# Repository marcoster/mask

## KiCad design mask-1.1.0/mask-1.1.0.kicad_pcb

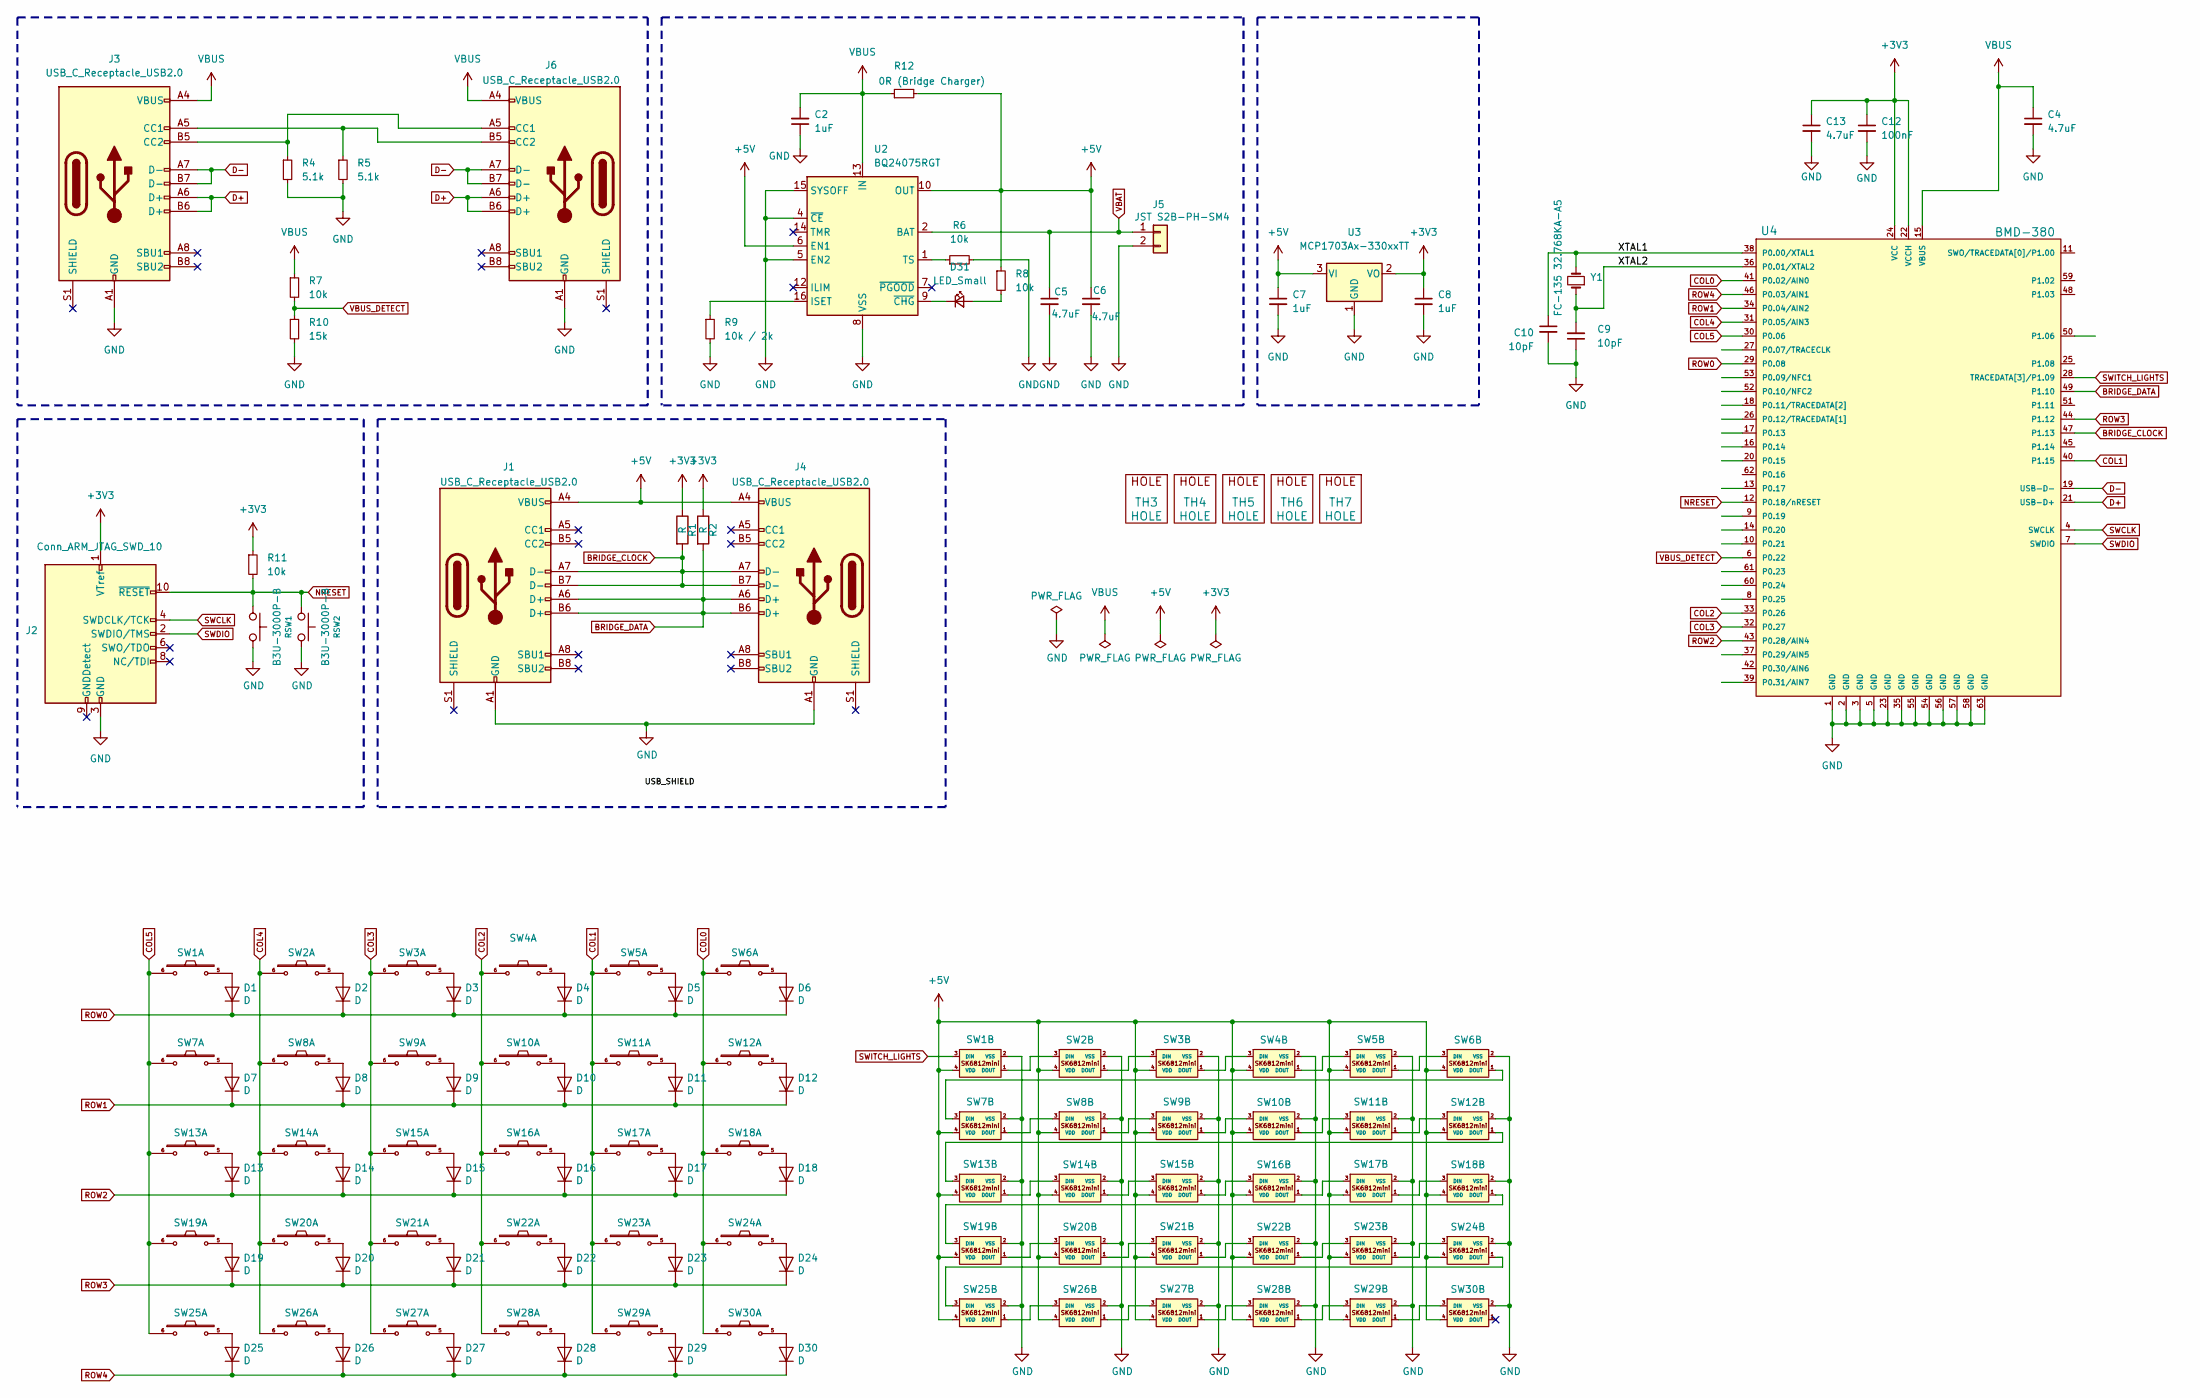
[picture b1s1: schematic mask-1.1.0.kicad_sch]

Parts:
C2, C7, C8: 1uF; C_0603_1608Metric
C4, C5, C6, C13: 4.7uF; C_0603_1608Metric
C9, C10: 10pF; C_0402_1005Metric
C12: 100nF; C_0603_1608Metric
D1, D2, D3, D4, D5, D6, D7, D8, D9, D10, D11, D12, D13, D14, D15, D16, D17, D18, D19, D20, D21, D22, D23, D24, D25, D26, D27, D28, D29, D30: D; crkbd-diode
D31: LED_Small; LED_0603_1608Metric
J1, J6: USB_C_Receptacle_USB2.0; USB_C_Receptacle_GCT_USB4505-xx-A_16P_TopMnt_Horizontal_NO_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
J2: Conn_ARM_JTAG_SWD_10; Tag-Connect_TC2050-IDC-NL_2x05_P1.27mm_Vertical
J3, J4: USB_C_Receptacle_USB2.0; USB_C_Receptacle_GCT_USB4505-xx-A_16P_TopMnt_Horizontal
J5: JST S2B-PH-SM4; JST_PH_S2B-PH-K_1x02_P2.00mm_Horizontal
R1, R2: R; R_0603_1608Metric
R4, R5: 5.1k; R_0603_1608Metric
R6, R7, R8, R11: 10k; R_0603_1608Metric
R9: 10k / 2k; R_0603_1608Metric
R10: 15k; R_0603_1608Metric
R12: 0R (Bridge Charger); R_0603_1608Metric
RSW1, RSW2: B3U-3000P-B; SW_SPST_B3U-3000P-B
SW1, SW2, SW3, SW4, SW5, SW6, SW7, SW8, SW9, SW10, SW11, SW12, SW13, SW14, SW15, SW16, SW17, SW18, SW19, SW20, SW21, SW22, SW23, SW24, SW25, SW26, SW27, SW28, SW29, SW30: SW_PUSH-MX_W_LED; SK6812MINI-E_and_cherry
TH3, TH4, TH5, TH6, TH7: HOLE; HOLE_M2_TH
U2: BQ24075RGT; VQFN-16-1EP_3x3mm_P0.5mm_EP1.6x1.6mm
U3: MCP1703Ax-330xxTT; SOT-23
U4: BMD-380
Y1: FC-135 32.768KA-A5; Crystal_SMD_MicroCrystal_CC7V-T1A-2Pin_3.2x1.5mm

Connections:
+3V3: C8.1, C12.1, C13.1, J2.1 (VTref), R1.1, R2.1, R11.1, U3.2 (VO), U4.22 (VCCH), U4.24 (VCC)
+5V: C6.1, C7.1, J1.A4 (VBUS), J1.A9 (VBUS), J1.B4 (VBUS), J1.B9 (VBUS), J4.A4 (VBUS), J4.A9 (VBUS), J4.B4 (VBUS), J4.B9 (VBUS), R8.1, R12.2, SW1.4 (VDD), SW2.4 (VDD), SW3.4 (VDD), SW4.4 (VDD), SW5.4 (VDD), SW6.4 (VDD), SW7.4 (VDD), SW8.4 (VDD), SW9.4 (VDD), SW10.4 (VDD), SW11.4 (VDD), SW12.4 (VDD), SW13.4 (VDD), SW14.4 (VDD), SW15.4 (VDD), SW16.4 (VDD), SW17.4 (VDD), SW18.4 (VDD), SW19.4 (VDD), SW20.4 (VDD), SW21.4 (VDD), SW22.4 (VDD), SW23.4 (VDD), SW24.4 (VDD), SW25.4 (VDD), SW26.4 (VDD), SW27.4 (VDD), SW28.4 (VDD), SW29.4 (VDD), SW30.4 (VDD), U2.6 (EN1), U2.10 (OUT), U2.11 (OUT), U3.3 (VI)
/XTAL1: C10.1, U4.38 (P0.00/XTAL1), Y1.2
/XTAL2: C9.2, U4.36 (P0.01/XTAL2), Y1.1
BRIDGE_CLOCK: J1.A7 (D-), J1.B7 (D-), J4.A7 (D-), J4.B7 (D-), R1.2, U4.47 (P1.13)
BRIDGE_DATA: J1.A6 (D+), J1.B6 (D+), J4.A6 (D+), J4.B6 (D+), R2.2, U4.49 (P1.10)
COL0: SW6.6, SW12.6, SW18.6, SW24.6, SW30.6, U4.41 (P0.02/AIN0)
COL1: SW5.6, SW11.6, SW17.6, SW23.6, SW29.6, U4.40 (P1.15)
COL2: SW4.6, SW10.6, SW16.6, SW22.6, SW28.6, U4.33 (P0.26)
COL3: SW3.6, SW9.6, SW15.6, SW21.6, SW27.6, U4.32 (P0.27)
COL4: SW2.6, SW8.6, SW14.6, SW20.6, SW26.6, U4.31 (P0.05/AIN3)
COL5: SW1.6, SW7.6, SW13.6, SW19.6, SW25.6, U4.30 (P0.06)
D+: J3.A6 (D+), J3.B6 (D+), J6.A6 (D+), J6.B6 (D+), U4.21 (USB-D+)
D-: J3.A7 (D-), J3.B7 (D-), J6.A7 (D-), J6.B7 (D-), U4.19 (USB-D-)
GND: C2.1, C4.2, C5.2, C6.2, C7.2, C8.2, C9.1, C10.2, C12.2, C13.2, J1.A1 (GND), J1.A12 (GND), J1.B1 (GND), J1.B12 (GND), J2.3 (GND), J2.5 (GND), J3.A1 (GND), J3.A12 (GND), J3.B1 (GND), J3.B12 (GND), J4.A1 (GND), J4.A12 (GND), J4.B1 (GND), J4.B12 (GND), J5.2, J6.A1 (GND), J6.A12 (GND), J6.B1 (GND), J6.B12 (GND), R4.2, R5.2, R6.2, R9.2, R10.2, RSW1.1, RSW2.2, SW1.2 (VSS), SW2.2 (VSS), SW3.2 (VSS), SW4.2 (VSS), SW5.2 (VSS), SW6.2 (VSS), SW7.2 (VSS), SW8.2 (VSS), SW9.2 (VSS), SW10.2 (VSS), SW11.2 (VSS), SW12.2 (VSS), SW13.2 (VSS), SW14.2 (VSS), SW15.2 (VSS), SW16.2 (VSS), SW17.2 (VSS), SW18.2 (VSS), SW19.2 (VSS), SW20.2 (VSS), SW21.2 (VSS), SW22.2 (VSS), SW23.2 (VSS), SW24.2 (VSS), SW25.2 (VSS), SW26.2 (VSS), SW27.2 (VSS), SW28.2 (VSS), SW29.2 (VSS), SW30.2 (VSS), U2.4 (~CE), U2.5 (EN2), U2.8 (VSS), U2.15 (SYSOFF), U2.17 (VSS), U3.1 (GND), U4.1 (GND), U4.2 (GND), U4.3 (GND), U4.5 (GND), U4.23 (GND), U4.35 (GND), U4.54 (GND), U4.55 (GND), U4.56 (GND), U4.57 (GND), U4.58 (GND), U4.63 (GND)
NRESET: J2.10 (~RESET), R11.2, RSW1.2, RSW2.1, U4.12 (P0.18/nRESET)
unnamed: D1.2 (A), SW1.5
unnamed: D2.2 (A), SW2.5
unnamed: D3.2 (A), SW3.5
unnamed: D4.2 (A), SW4.5
unnamed: D5.2 (A), SW5.5
unnamed: D6.2 (A), SW6.5
unnamed: D7.2 (A), SW7.5
unnamed: D8.2 (A), SW8.5
unnamed: D9.2 (A), SW9.5
unnamed: D10.2 (A), SW10.5
unnamed: D11.2 (A), SW11.5
unnamed: D12.2 (A), SW12.5
unnamed: D13.2 (A), SW13.5
unnamed: D14.2 (A), SW14.5
unnamed: D15.2 (A), SW15.5
unnamed: D16.2 (A), SW16.5
unnamed: D17.2 (A), SW17.5
unnamed: D18.2 (A), SW18.5
unnamed: D19.2 (A), SW19.5
unnamed: D20.2 (A), SW20.5
unnamed: D21.2 (A), SW21.5
unnamed: D22.2 (A), SW22.5
unnamed: D23.2 (A), SW23.5
unnamed: D24.2 (A), SW24.5
unnamed: D25.2 (A), SW25.5
unnamed: D26.2 (A), SW26.5
unnamed: D27.2 (A), SW27.5
unnamed: D28.2 (A), SW28.5
unnamed: D29.2 (A), SW29.5
unnamed: D30.2 (A), SW30.5
unnamed: D31.2 (A), R8.2
unnamed: D31.1 (K), U2.9 (~CHG)
unnamed: J3.A5 (CC1), J6.B5 (CC2), R5.1
unnamed: J3.B5 (CC2), J6.A5 (CC1), R4.1
unnamed: SW1.1 (DOUT), SW2.3 (DIN)
unnamed: SW2.1 (DOUT), SW3.3 (DIN)
unnamed: SW3.1 (DOUT), SW4.3 (DIN)
unnamed: SW4.1 (DOUT), SW5.3 (DIN)
unnamed: SW5.1 (DOUT), SW6.3 (DIN)
unnamed: SW6.1 (DOUT), SW7.3 (DIN)
unnamed: SW7.1 (DOUT), SW8.3 (DIN)
unnamed: SW8.1 (DOUT), SW9.3 (DIN)
unnamed: SW9.1 (DOUT), SW10.3 (DIN)
unnamed: SW10.1 (DOUT), SW11.3 (DIN)
unnamed: SW11.1 (DOUT), SW12.3 (DIN)
unnamed: SW12.1 (DOUT), SW13.3 (DIN)
unnamed: SW13.1 (DOUT), SW14.3 (DIN)
unnamed: SW14.1 (DOUT), SW15.3 (DIN)
unnamed: SW15.1 (DOUT), SW16.3 (DIN)
unnamed: SW16.1 (DOUT), SW17.3 (DIN)
unnamed: SW17.1 (DOUT), SW18.3 (DIN)
unnamed: SW18.1 (DOUT), SW19.3 (DIN)
unnamed: SW19.1 (DOUT), SW20.3 (DIN)
unnamed: SW20.1 (DOUT), SW21.3 (DIN)
unnamed: SW21.1 (DOUT), SW22.3 (DIN)
unnamed: SW22.1 (DOUT), SW23.3 (DIN)
unnamed: SW23.1 (DOUT), SW24.3 (DIN)
unnamed: SW24.1 (DOUT), SW25.3 (DIN)
unnamed: SW25.1 (DOUT), SW26.3 (DIN)
unnamed: SW26.1 (DOUT), SW27.3 (DIN)
unnamed: SW27.1 (DOUT), SW28.3 (DIN)
unnamed: SW28.1 (DOUT), SW29.3 (DIN)
unnamed: SW29.1 (DOUT), SW30.3 (DIN)
unnamed: R9.1, U2.16 (ISET)
unnamed: R6.1, U2.1 (TS)
ROW0: D1.1 (K), D2.1 (K), D3.1 (K), D4.1 (K), D5.1 (K), D6.1 (K), U4.29 (P0.08)
ROW1: D7.1 (K), D8.1 (K), D9.1 (K), D10.1 (K), D11.1 (K), D12.1 (K), U4.34 (P0.04/AIN2)
ROW2: D13.1 (K), D14.1 (K), D15.1 (K), D16.1 (K), D17.1 (K), D18.1 (K), U4.43 (P0.28/AIN4)
ROW3: D19.1 (K), D20.1 (K), D21.1 (K), D22.1 (K), D23.1 (K), D24.1 (K), U4.44 (P1.12)
ROW4: D25.1 (K), D26.1 (K), D27.1 (K), D28.1 (K), D29.1 (K), D30.1 (K), U4.46 (P0.03/AIN1)
SWCLK: J2.4 (SWDCLK/TCK), U4.4 (SWCLK)
SWDIO: J2.2 (SWDIO/TMS), U4.7 (SWDIO)
SWITCH_LIGHTS: SW1.3 (DIN), U4.28 (TRACEDATA[3]/P1.09)
VBAT: C5.1, J5.1, U2.2 (BAT), U2.3 (BAT)
VBUS: C2.2, C4.1, J3.A4 (VBUS), J3.A9 (VBUS), J3.B4 (VBUS), J3.B9 (VBUS), J6.A4 (VBUS), J6.A9 (VBUS), J6.B4 (VBUS), J6.B9 (VBUS), R7.1, R12.1, U2.13 (IN), U4.15 (VBUS)
VBUS_DETECT: R7.2, R10.1, U4.6 (P0.22)

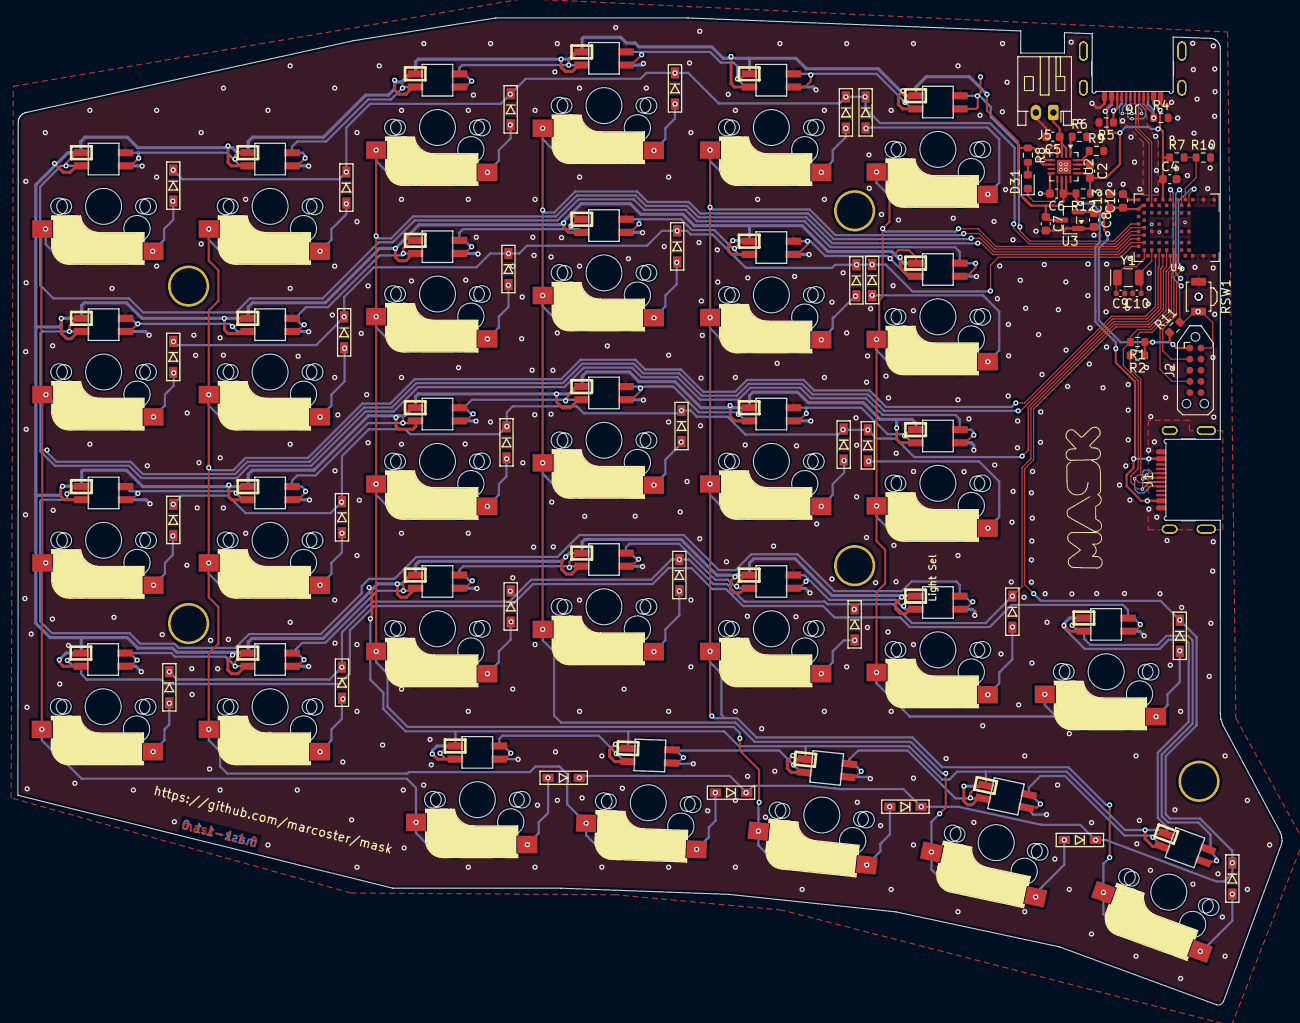
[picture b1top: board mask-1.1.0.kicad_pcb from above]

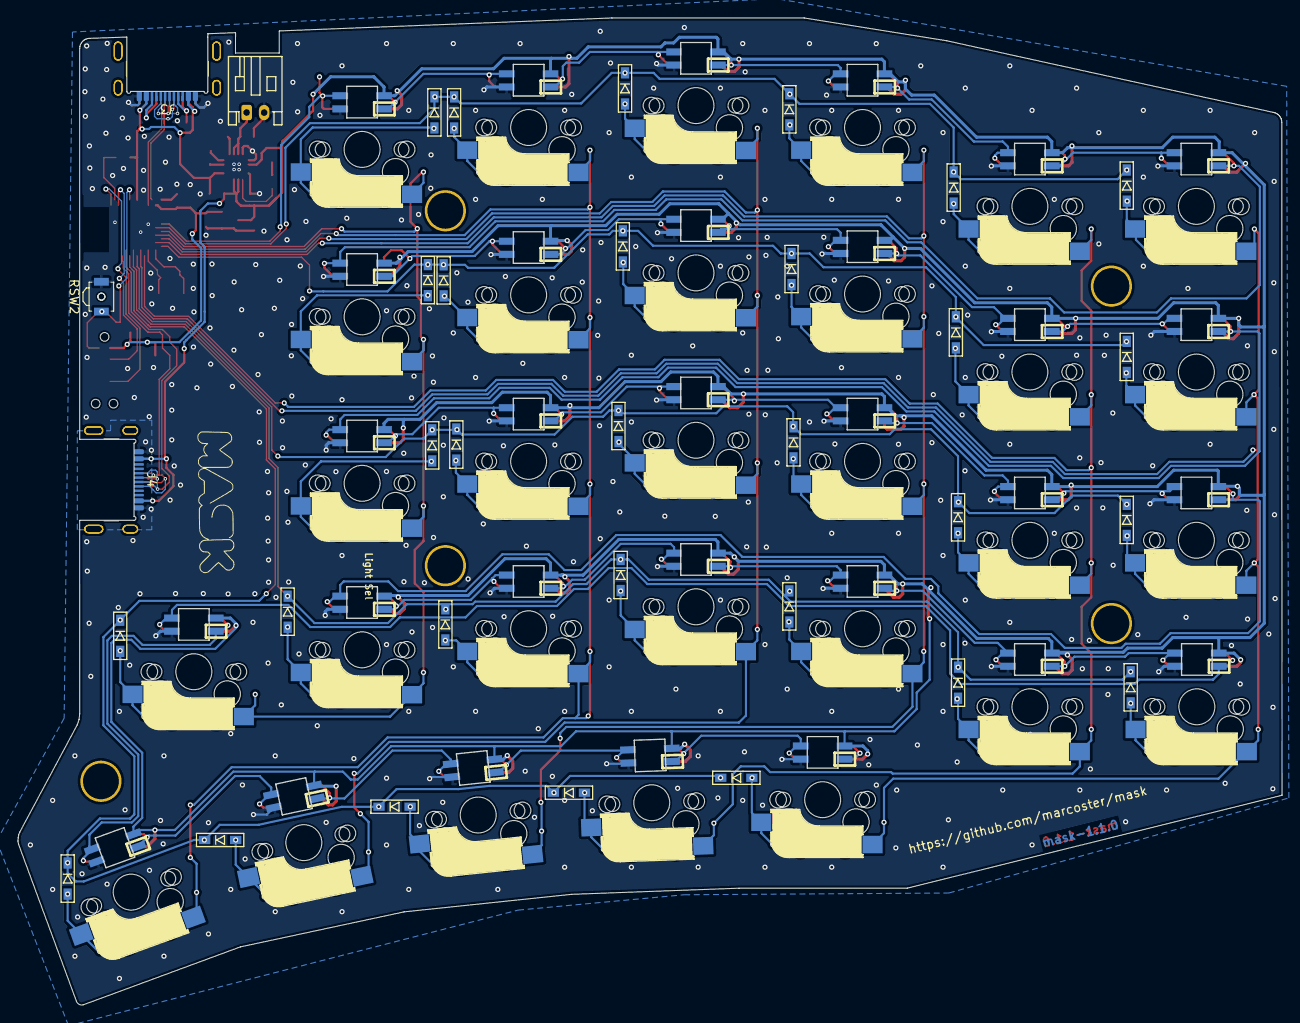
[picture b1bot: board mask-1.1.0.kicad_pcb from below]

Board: 2 copper layers, 144.2 x 112.6 mm, 99 parts (68 on the bottom side), 92 nets.

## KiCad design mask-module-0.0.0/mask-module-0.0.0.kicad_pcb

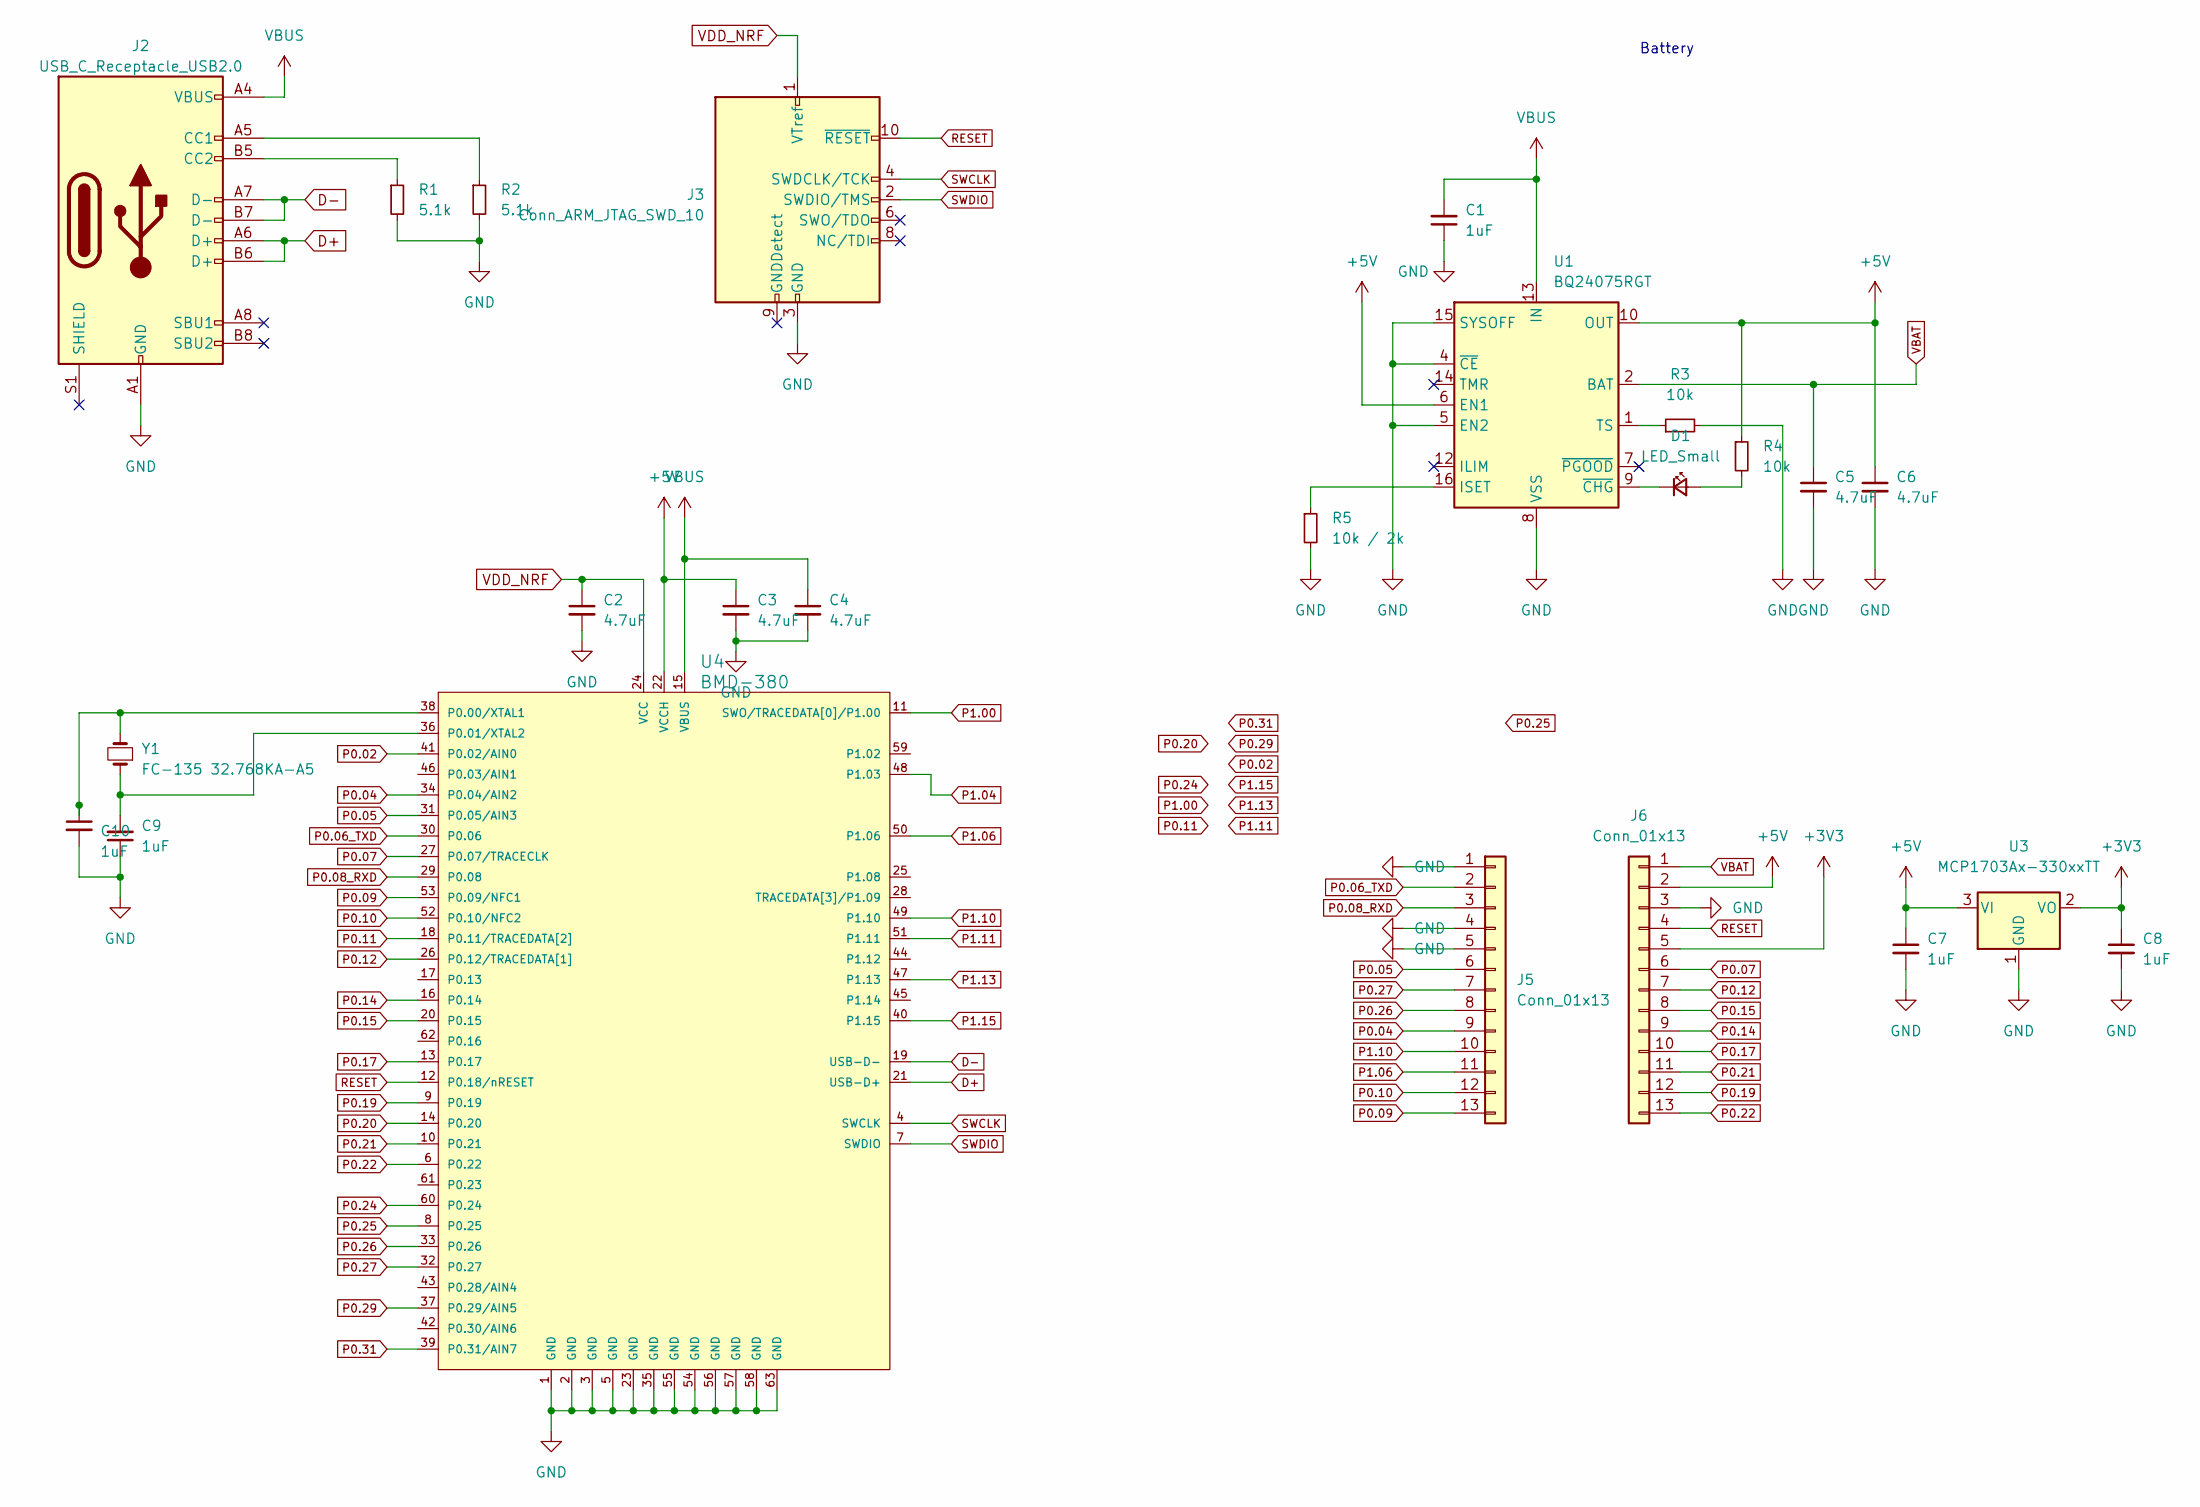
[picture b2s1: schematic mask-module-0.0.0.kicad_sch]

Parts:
C1, C7, C8, C9, C10: 1uF; C_0402_1005Metric
C2, C3, C4, C5, C6: 4.7uF; C_0603_1608Metric
D1: LED_Small; LED_0402_1005Metric
J2: USB_C_Receptacle_USB2.0; USB_C_Receptacle_JAE_DX07S016JA1R1500
J3: Conn_ARM_JTAG_SWD_10; Tag-Connect_TC2050-IDC-NL_2x05_P1.27mm_Vertical
J5, J6: Conn_01x13; PinHeader_1x13_P2.54mm_Vertical
R1, R2: 5.1k; R_0402_1005Metric
R3, R4: 10k; R_0402_1005Metric
R5: 10k / 2k; R_0402_1005Metric
U1: BQ24075RGT; VQFN-16-1EP_3x3mm_P0.5mm_EP1.6x1.6mm
U3: MCP1703Ax-330xxTT; SOT-23
U4: BMD-380
Y1: FC-135 32.768KA-A5; Crystal_SMD_MicroCrystal_CC7V-T1A-2Pin_3.2x1.5mm

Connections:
+3V3: C8.1, J6.5, U3.2 (VO)
+5V: C3.1, C6.1, C7.1, J6.2, R4.1, U1.6 (EN1), U1.10 (OUT), U1.11 (OUT), U3.3 (VI), U4.22 (VCCH)
D+: J2.A6 (D+), J2.B6 (D+), U4.21 (USB-D+)
D-: J2.A7 (D-), J2.B7 (D-), U4.19 (USB-D-)
GND: C1.1, C2.2, C3.2, C4.2, C5.2, C6.2, C7.2, C8.2, C9.1, C10.2, J2.A1 (GND), J2.A12 (GND), J2.B1 (GND), J2.B12 (GND), J3.3 (GND), J3.5 (GND), J5.1, J5.4, J5.5, J6.3, R1.2, R2.2, R3.2, R5.2, U1.4 (~CE), U1.5 (EN2), U1.8 (VSS), U1.15 (SYSOFF), U1.17 (VSS), U3.1 (GND), U4.1 (GND), U4.2 (GND), U4.3 (GND), U4.5 (GND), U4.23 (GND), U4.35 (GND), U4.54 (GND), U4.55 (GND), U4.56 (GND), U4.57 (GND), U4.58 (GND), U4.63 (GND)
unnamed: D1.2 (A), R4.2
unnamed: D1.1 (K), U1.9 (~CHG)
unnamed: J2.A5 (CC1), R2.1
unnamed: J2.B5 (CC2), R1.1
unnamed: R5.1, U1.16 (ISET)
unnamed: R3.1, U1.1 (TS)
unnamed: C10.1, U4.38 (P0.00/XTAL1), Y1.2
unnamed: C9.2, U4.36 (P0.01/XTAL2), Y1.1
P0.02: U4.41 (P0.02/AIN0)
P0.04: J5.9, U4.34 (P0.04/AIN2)
P0.05: J5.6, U4.31 (P0.05/AIN3)
P0.06_TXD: J5.2, U4.30 (P0.06)
P0.07: J6.6, U4.27 (P0.07/TRACECLK)
P0.08_RXD: J5.3, U4.29 (P0.08)
P0.09: J5.13, U4.53 (P0.09/NFC1)
P0.10: J5.12, U4.52 (P0.10/NFC2)
P0.11: U4.18 (P0.11/TRACEDATA[2])
P0.12: J6.7, U4.26 (P0.12/TRACEDATA[1])
P0.14: J6.9, U4.16 (P0.14)
P0.15: J6.8, U4.20 (P0.15)
P0.17: J6.10, U4.13 (P0.17)
P0.19: J6.12, U4.9 (P0.19)
P0.20: U4.14 (P0.20)
P0.21: J6.11, U4.10 (P0.21)
P0.22: J6.13, U4.6 (P0.22)
P0.24: U4.60 (P0.24)
P0.25: U4.8 (P0.25)
P0.26: J5.8, U4.33 (P0.26)
P0.27: J5.7, U4.32 (P0.27)
P0.29: U4.37 (P0.29/AIN5)
P0.31: U4.39 (P0.31/AIN7)
P1.00: U4.11 (SWO/TRACEDATA[0]/P1.00)
P1.04: U4.48 (P1.03)
P1.06: J5.11, U4.50 (P1.06)
P1.10: J5.10, U4.49 (P1.10)
P1.11: U4.51 (P1.11)
P1.13: U4.47 (P1.13)
P1.15: U4.40 (P1.15)
RESET: J3.10 (~RESET), J6.4, U4.12 (P0.18/nRESET)
SWCLK: J3.4 (SWDCLK/TCK), U4.4 (SWCLK)
SWDIO: J3.2 (SWDIO/TMS), U4.7 (SWDIO)
VBAT: C5.1, J6.1, U1.2 (BAT), U1.3 (BAT)
VBUS: C1.2, C4.1, J2.A4 (VBUS), J2.A9 (VBUS), J2.B4 (VBUS), J2.B9 (VBUS), U1.13 (IN), U4.15 (VBUS)
VDD_NRF: C2.1, J3.1 (VTref), U4.24 (VCC)

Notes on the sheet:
Battery

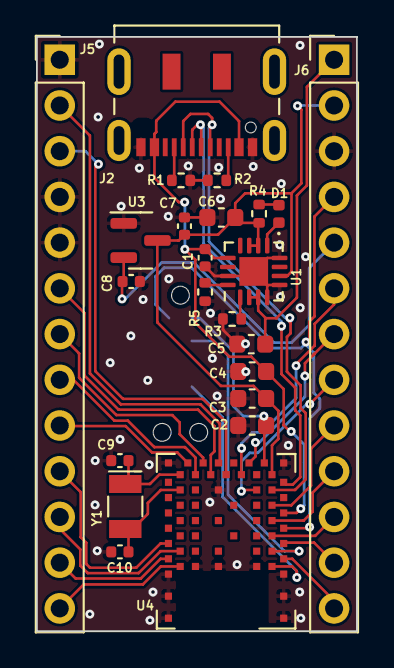
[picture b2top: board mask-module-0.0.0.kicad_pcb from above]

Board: 2 copper layers, 17.8 x 33.0 mm, 24 parts (1 on the bottom side), 37 nets.

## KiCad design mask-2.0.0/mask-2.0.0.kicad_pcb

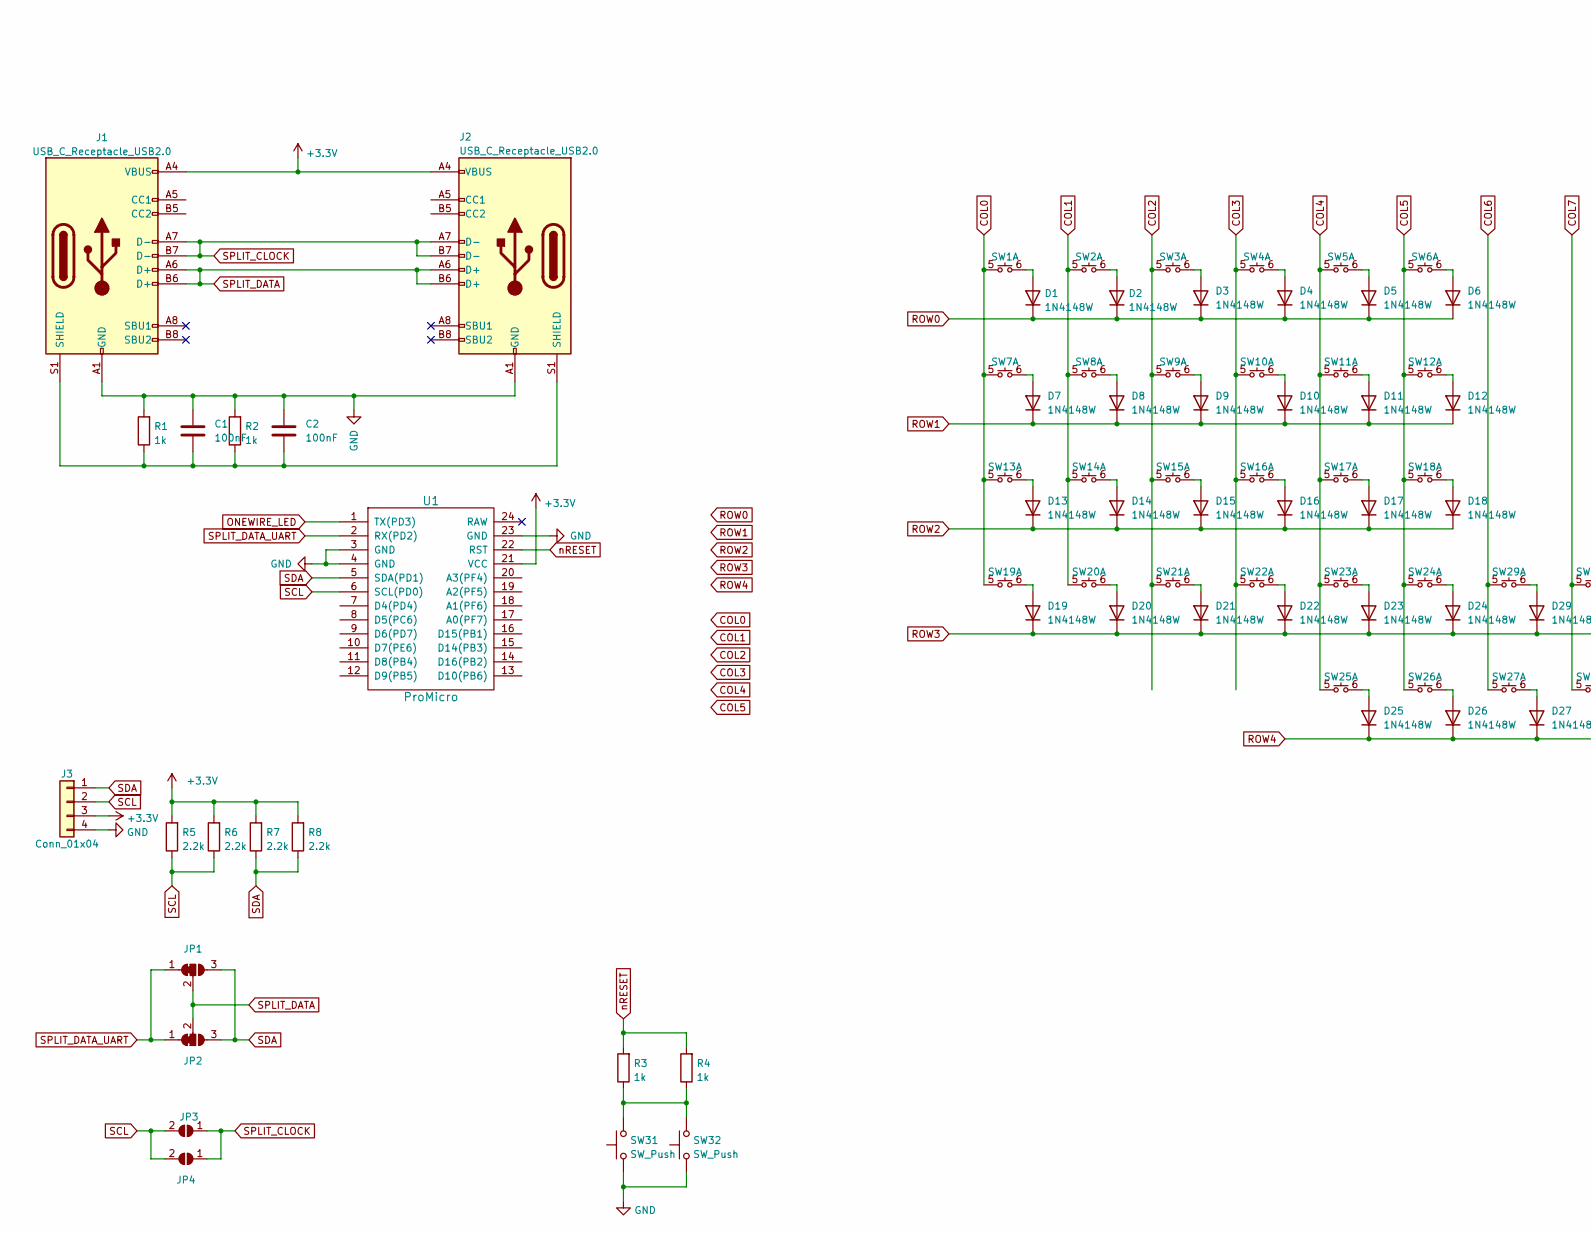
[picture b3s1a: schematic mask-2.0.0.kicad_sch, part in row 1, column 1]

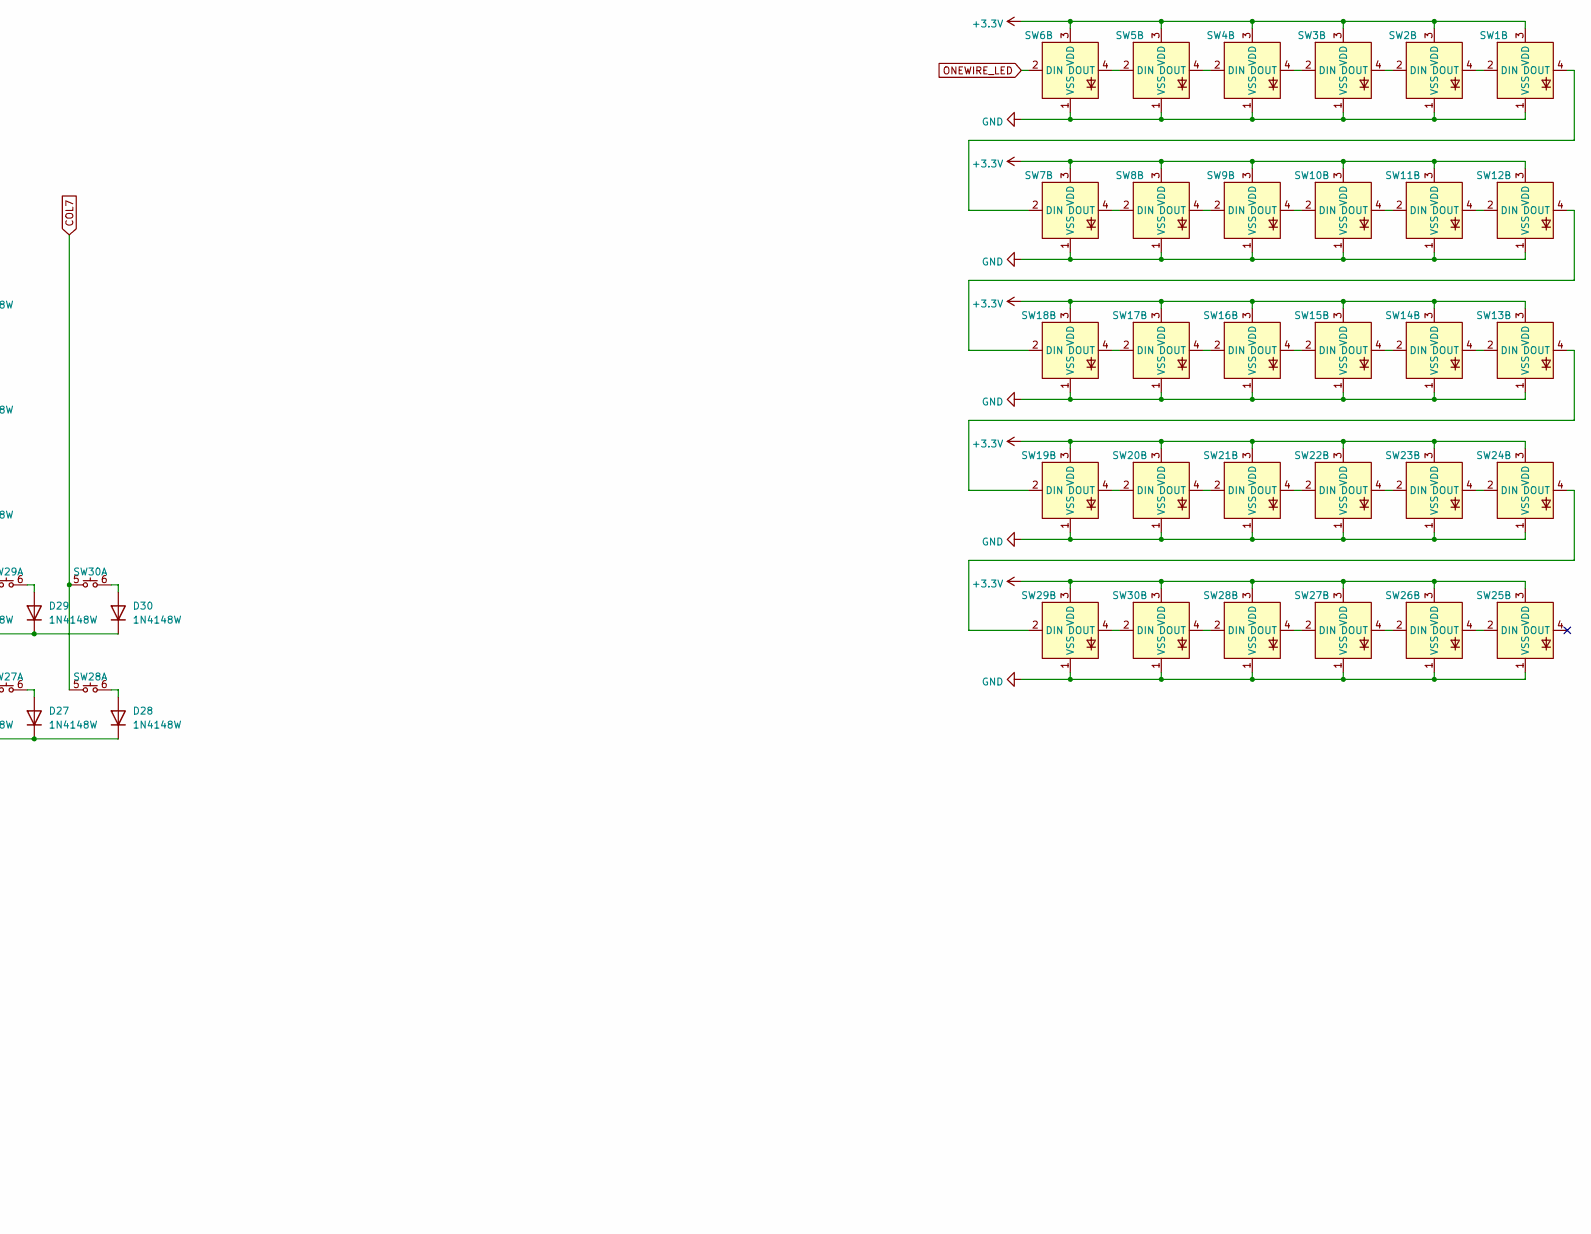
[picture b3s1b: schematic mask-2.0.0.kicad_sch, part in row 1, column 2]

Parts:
C1, C2: 100nF; C_0603_1608Metric
D1, D2, D3, D4, D5, D6, D7, D8, D9, D10, D11, D12, D13, D14, D15, D16, D17, D18, D19, D20, D21, D22, D23, D24, D25, D26, D27, D28, D29, D30: 1N4148W; D_0603_1608Metric_TopBottom
J1, J2: USB_C_Receptacle_USB2.0; USB_C_Receptacle_JAE_DX07S016JA1R1500
J3: Conn_01x04; PinHeader_1x04_P2.54mm_Vertical
JP1, JP2: SolderJumper_3_Bridged12; SolderJumper-3_P1.3mm_Bridged12_RoundedPad1.0x1.5mm_NumberL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
JP3, JP4: SolderJumper_2_Open; SolderJumper-2_P1.3mm_Open_RoundedPad1.0x1.5mm
R1, R2, R3, R4: 1k; R_0603_1608Metric
R5, R6, R7, R8: 2.2k; R_0603_1608Metric
SW1, SW2, SW3, SW4, SW5, SW6, SW7, SW8, SW9, SW10, SW11, SW12, SW13, SW14, SW15, SW16, SW17, SW18, SW19, SW20, SW21, SW22, SW23, SW24, SW25, SW26, SW27, SW28, SW29, SW30: Cherry_MX_ULP_SK6812_1515; Cherry_MX_ULP_SK6812_1515_TopBottom
SW31, SW32: SW_Push; SW_SPST_B3U-1000P
U1: ProMicro; KB2040_SMD

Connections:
+3.3V: J1.A4 (VBUS), J1.A9 (VBUS), J1.B4 (VBUS), J1.B9 (VBUS), J2.A4 (VBUS), J2.A9 (VBUS), J2.B4 (VBUS), J2.B9 (VBUS), J3.3, R5.2, R6.2, R7.2, R8.2, SW1.3 (VDD), SW2.3 (VDD), SW3.3 (VDD), SW4.3 (VDD), SW5.3 (VDD), SW6.3 (VDD), SW7.3 (VDD), SW8.3 (VDD), SW9.3 (VDD), SW10.3 (VDD), SW11.3 (VDD), SW12.3 (VDD), SW13.3 (VDD), SW14.3 (VDD), SW15.3 (VDD), SW16.3 (VDD), SW17.3 (VDD), SW18.3 (VDD), SW19.3 (VDD), SW20.3 (VDD), SW21.3 (VDD), SW22.3 (VDD), SW23.3 (VDD), SW24.3 (VDD), SW25.3 (VDD), SW26.3 (VDD), SW27.3 (VDD), SW28.3 (VDD), SW29.3 (VDD), SW30.3 (VDD), U1.21 (VCC)
COL0: SW1.5, SW7.5, SW13.5, SW19.5
COL1: SW2.5, SW8.5, SW14.5, SW20.5
COL2: SW3.5, SW9.5, SW15.5, SW21.5
COL3: SW4.5, SW10.5, SW16.5, SW22.5
COL4: SW5.5, SW11.5, SW17.5, SW23.5, SW25.5
COL5: SW6.5, SW12.5, SW18.5, SW24.5, SW26.5
COL6: SW27.5, SW29.5
COL7: SW28.5, SW30.5
GND: C1.1, C2.1, J1.A1 (GND), J1.A12 (GND), J1.B1 (GND), J1.B12 (GND), J2.A1 (GND), J2.A12 (GND), J2.B1 (GND), J2.B12 (GND), J3.4, R1.2, R2.2, SW1.1 (VSS), SW2.1 (VSS), SW3.1 (VSS), SW4.1 (VSS), SW5.1 (VSS), SW6.1 (VSS), SW7.1 (VSS), SW8.1 (VSS), SW9.1 (VSS), SW10.1 (VSS), SW11.1 (VSS), SW12.1 (VSS), SW13.1 (VSS), SW14.1 (VSS), SW15.1 (VSS), SW16.1 (VSS), SW17.1 (VSS), SW18.1 (VSS), SW19.1 (VSS), SW20.1 (VSS), SW21.1 (VSS), SW22.1 (VSS), SW23.1 (VSS), SW24.1 (VSS), SW25.1 (VSS), SW26.1 (VSS), SW27.1 (VSS), SW28.1 (VSS), SW29.1 (VSS), SW30.1 (VSS), SW31.1, SW32.1, U1.3 (GND), U1.4 (GND), U1.23 (GND)
unnamed: C1.2, C2.2, J1.S1 (SHIELD), J2.S1 (SHIELD), R1.1, R2.1
unnamed: D1.2 (A), SW1.6
unnamed: D2.2 (A), SW2.6
unnamed: D3.2 (A), SW3.6
unnamed: D4.2 (A), SW4.6
unnamed: D5.2 (A), SW5.6
unnamed: D6.2 (A), SW6.6
unnamed: D7.2 (A), SW7.6
unnamed: D8.2 (A), SW8.6
unnamed: D9.2 (A), SW9.6
unnamed: D10.2 (A), SW10.6
unnamed: D11.2 (A), SW11.6
unnamed: D12.2 (A), SW12.6
unnamed: D13.2 (A), SW13.6
unnamed: D14.2 (A), SW14.6
unnamed: D15.2 (A), SW15.6
unnamed: D16.2 (A), SW16.6
unnamed: D17.2 (A), SW17.6
unnamed: D18.2 (A), SW18.6
unnamed: D19.2 (A), SW19.6
unnamed: D20.2 (A), SW20.6
unnamed: D21.2 (A), SW21.6
unnamed: D22.2 (A), SW22.6
unnamed: D23.2 (A), SW23.6
unnamed: D24.2 (A), SW24.6
unnamed: D25.2 (A), SW25.6
unnamed: D26.2 (A), SW26.6
unnamed: D27.2 (A), SW27.6
unnamed: D28.2 (A), SW28.6
unnamed: D29.2 (A), SW29.6
unnamed: D30.2 (A), SW30.6
unnamed: R3.1, R4.1, SW31.2, SW32.2
unnamed: SW2.2 (DIN), SW3.4 (DOUT)
unnamed: SW1.2 (DIN), SW2.4 (DOUT)
unnamed: SW3.2 (DIN), SW4.4 (DOUT)
unnamed: SW4.2 (DIN), SW5.4 (DOUT)
unnamed: SW5.2 (DIN), SW6.4 (DOUT)
unnamed: SW1.4 (DOUT), SW7.2 (DIN)
unnamed: SW7.4 (DOUT), SW8.2 (DIN)
unnamed: SW8.4 (DOUT), SW9.2 (DIN)
unnamed: SW9.4 (DOUT), SW10.2 (DIN)
unnamed: SW10.4 (DOUT), SW11.2 (DIN)
unnamed: SW11.4 (DOUT), SW12.2 (DIN)
unnamed: SW12.4 (DOUT), SW18.2 (DIN)
unnamed: SW13.2 (DIN), SW14.4 (DOUT)
unnamed: SW15.2 (DIN), SW16.4 (DOUT)
unnamed: SW14.2 (DIN), SW15.4 (DOUT)
unnamed: SW16.2 (DIN), SW17.4 (DOUT)
unnamed: SW17.2 (DIN), SW18.4 (DOUT)
unnamed: SW13.4 (DOUT), SW19.2 (DIN)
unnamed: SW19.4 (DOUT), SW20.2 (DIN)
unnamed: SW20.4 (DOUT), SW21.2 (DIN)
unnamed: SW21.4 (DOUT), SW22.2 (DIN)
unnamed: SW22.4 (DOUT), SW23.2 (DIN)
unnamed: SW23.4 (DOUT), SW24.2 (DIN)
unnamed: SW24.4 (DOUT), SW29.2 (DIN)
unnamed: SW25.2 (DIN), SW26.4 (DOUT)
unnamed: SW26.2 (DIN), SW27.4 (DOUT)
unnamed: SW27.2 (DIN), SW28.4 (DOUT)
unnamed: SW29.4 (DOUT), SW30.2 (DIN)
unnamed: SW28.2 (DIN), SW30.4 (DOUT)
ONEWIRE_LED: SW6.2 (DIN), U1.1 (TX(PD3))
ROW0: D1.1 (K), D2.1 (K), D3.1 (K), D4.1 (K), D5.1 (K), D6.1 (K)
ROW1: D7.1 (K), D8.1 (K), D9.1 (K), D10.1 (K), D11.1 (K), D12.1 (K)
ROW2: D13.1 (K), D14.1 (K), D15.1 (K), D16.1 (K), D17.1 (K), D18.1 (K)
ROW3: D19.1 (K), D20.1 (K), D21.1 (K), D22.1 (K), D23.1 (K), D24.1 (K), D29.1 (K), D30.1 (K)
ROW4: D25.1 (K), D26.1 (K), D27.1 (K), D28.1 (K)
SCL: J3.2, JP3.2 (B), JP4.2 (B), R5.1, R6.1, U1.6 (SCL(PD0))
SDA: J3.1, JP1.3 (B), JP2.3 (B), R7.1, R8.1, U1.5 (SDA(PD1))
SPLIT_CLOCK: J1.A7 (D-), J1.B7 (D-), J2.A7 (D-), J2.B7 (D-), JP3.1 (A), JP4.1 (A)
SPLIT_DATA: J1.A6 (D+), J1.B6 (D+), J2.A6 (D+), J2.B6 (D+), JP1.2 (C), JP2.2 (C)
SPLIT_DATA_UART: JP1.1 (A), JP2.1 (A), U1.2 (RX(PD2))
nRESET: R3.2, R4.2, U1.22 (RST)
